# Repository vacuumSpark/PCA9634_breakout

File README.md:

# PCA9634_breakout
Breakout board featuring 8 LEDs driven by the PCA9634 I2C PWM led driver

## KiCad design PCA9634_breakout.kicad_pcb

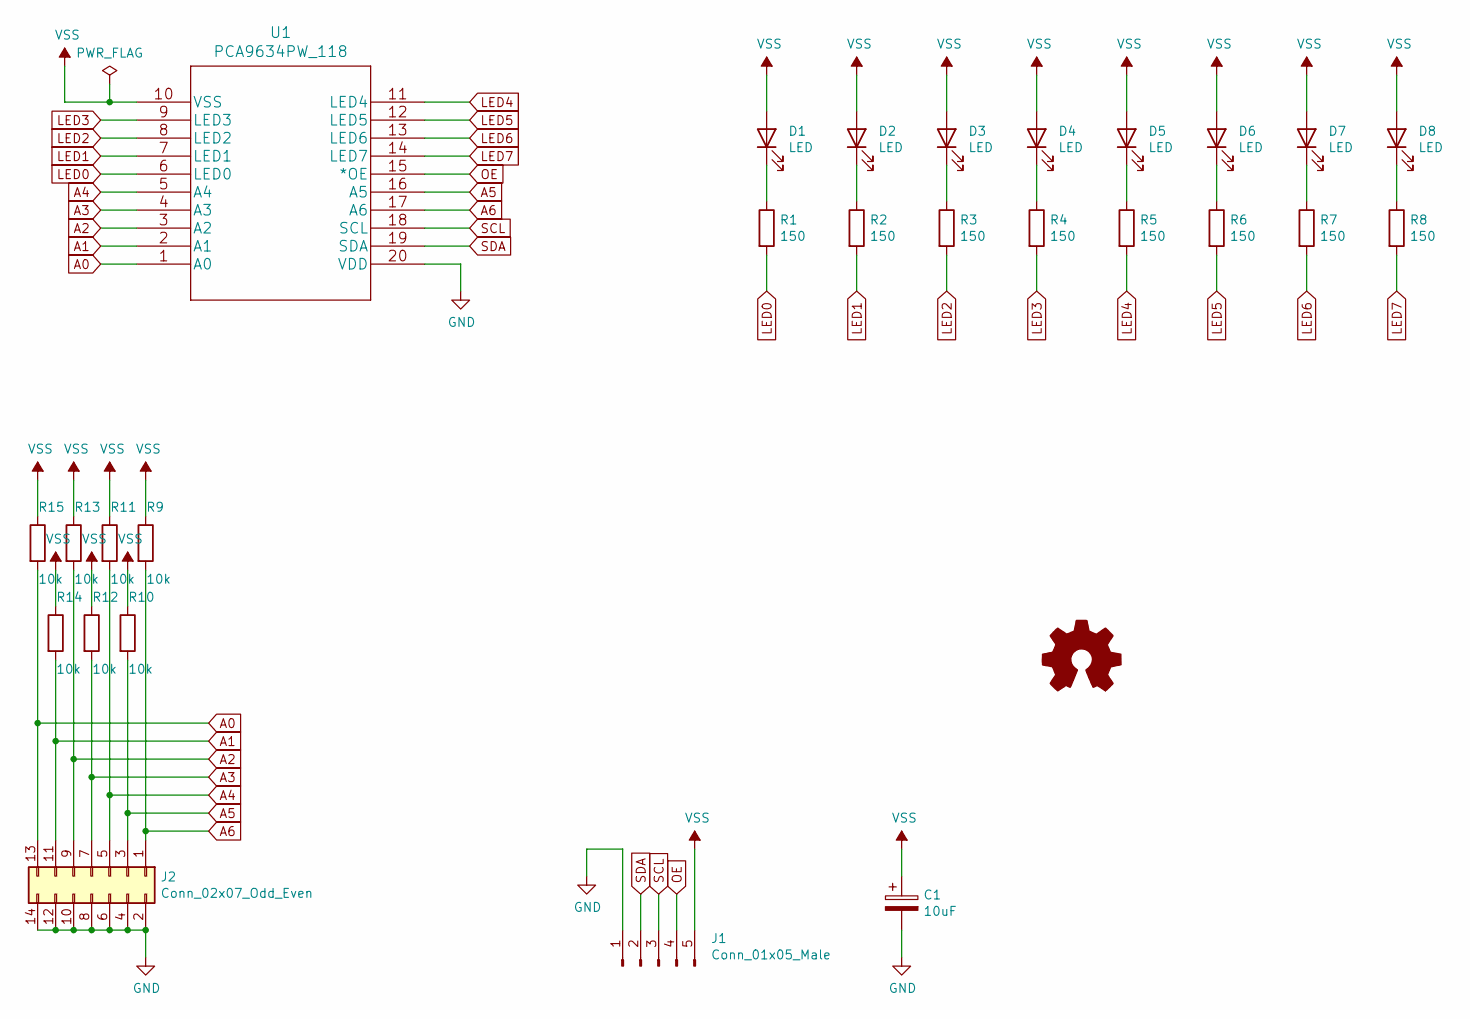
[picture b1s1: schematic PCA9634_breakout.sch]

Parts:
C1: 10uF; CP_EIA-3216-18_Kemet-A; JLCPCB C7171
D1: LED; LED_0805_2012Metric_Castellated; JLCPCB C2296
D2, D3, D4, D5, D6, D7, D8: LED; LED_0805_2012Metric_Castellated
J1: Conn_01x05_Male; PinHeader_1x05_P2.54mm_Vertical
J2: Conn_02x07_Odd_Even; PinHeader_2x07_P2.54mm_Vertical
R1: 150; R_0805_2012Metric; JLCPCB C17471
R2, R3, R4, R5, R6, R7, R8: 150; R_0805_2012Metric
R9, R10, R11, R12, R13, R14, R15: 10k; R_0805_2012Metric; JLCPCB C17471
U1: PCA9634PW_118; SOIC-20W_7.5x12.8mm_P1.27mm

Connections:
A0: J2.13, R15.2, U1.1 (A0)
A1: J2.11, R14.2, U1.2 (A1)
A2: J2.9, R13.2, U1.3 (A2)
A3: J2.7, R12.2, U1.4 (A3)
A4: J2.5, R11.2, U1.5 (A4)
A5: J2.3, R10.2, U1.16 (A5)
A6: J2.1, R9.2, U1.17 (A6)
GND: C1.2, J1.1, J2.2, J2.4, J2.6, J2.8, J2.10, J2.12, J2.14, U1.20 (VDD)
LED0: R1.2, U1.6 (LED0)
LED1: R2.2, U1.7 (LED1)
LED2: R3.2, U1.8 (LED2)
LED3: R4.2, U1.9 (LED3)
LED4: R5.2, U1.11 (LED4)
LED5: R6.2, U1.12 (LED5)
LED6: R7.2, U1.13 (LED6)
LED7: R8.2, U1.14 (LED7)
unnamed: D1.1 (K), R1.1
unnamed: D2.1 (K), R2.1
unnamed: D3.1 (K), R3.1
unnamed: D4.1 (K), R4.1
unnamed: D5.1 (K), R5.1
unnamed: D6.1 (K), R6.1
unnamed: D7.1 (K), R7.1
unnamed: D8.1 (K), R8.1
OE: J1.4, U1.15 (*OE)
SCL: J1.3, U1.18 (SCL)
SDA: J1.2, U1.19 (SDA)
VSS: C1.1, D1.2 (A), D2.2 (A), D3.2 (A), D4.2 (A), D5.2 (A), D6.2 (A), D7.2 (A), D8.2 (A), J1.5, R9.1, R10.1, R11.1, R12.1, R13.1, R14.1, R15.1, U1.10 (VSS)

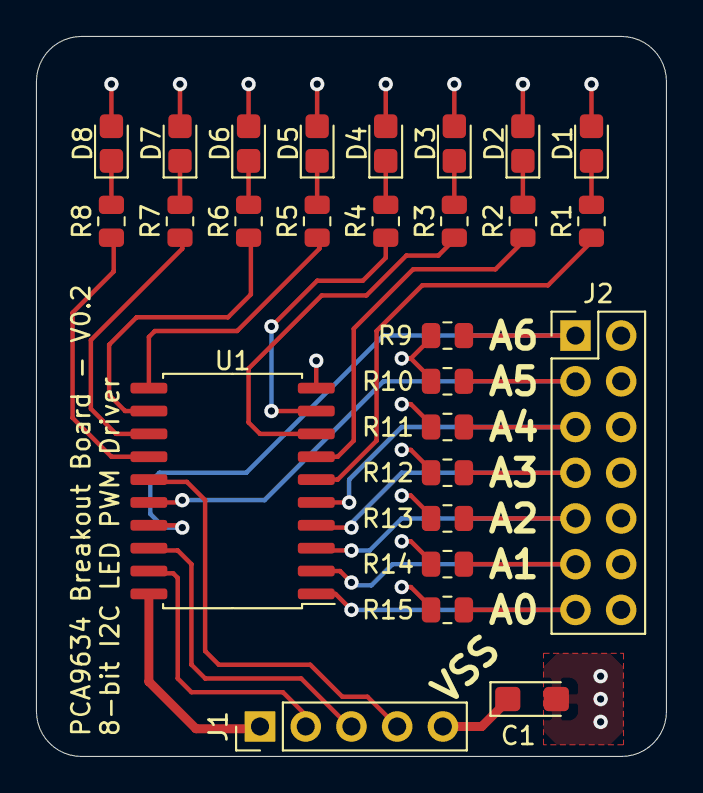
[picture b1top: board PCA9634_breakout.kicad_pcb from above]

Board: 4 copper layers, 35.0 x 40.0 mm, 27 parts (0 on the bottom side), 28 nets.

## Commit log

2021-09-24 feat: Changed footprints such that they are featured in the JLCPCB SMT assembly service as basic parts.
2021-10-21 changed solder jumper to double row pin 2.54 connector on top side
2021-10-21 converted to 4 layer pcb
